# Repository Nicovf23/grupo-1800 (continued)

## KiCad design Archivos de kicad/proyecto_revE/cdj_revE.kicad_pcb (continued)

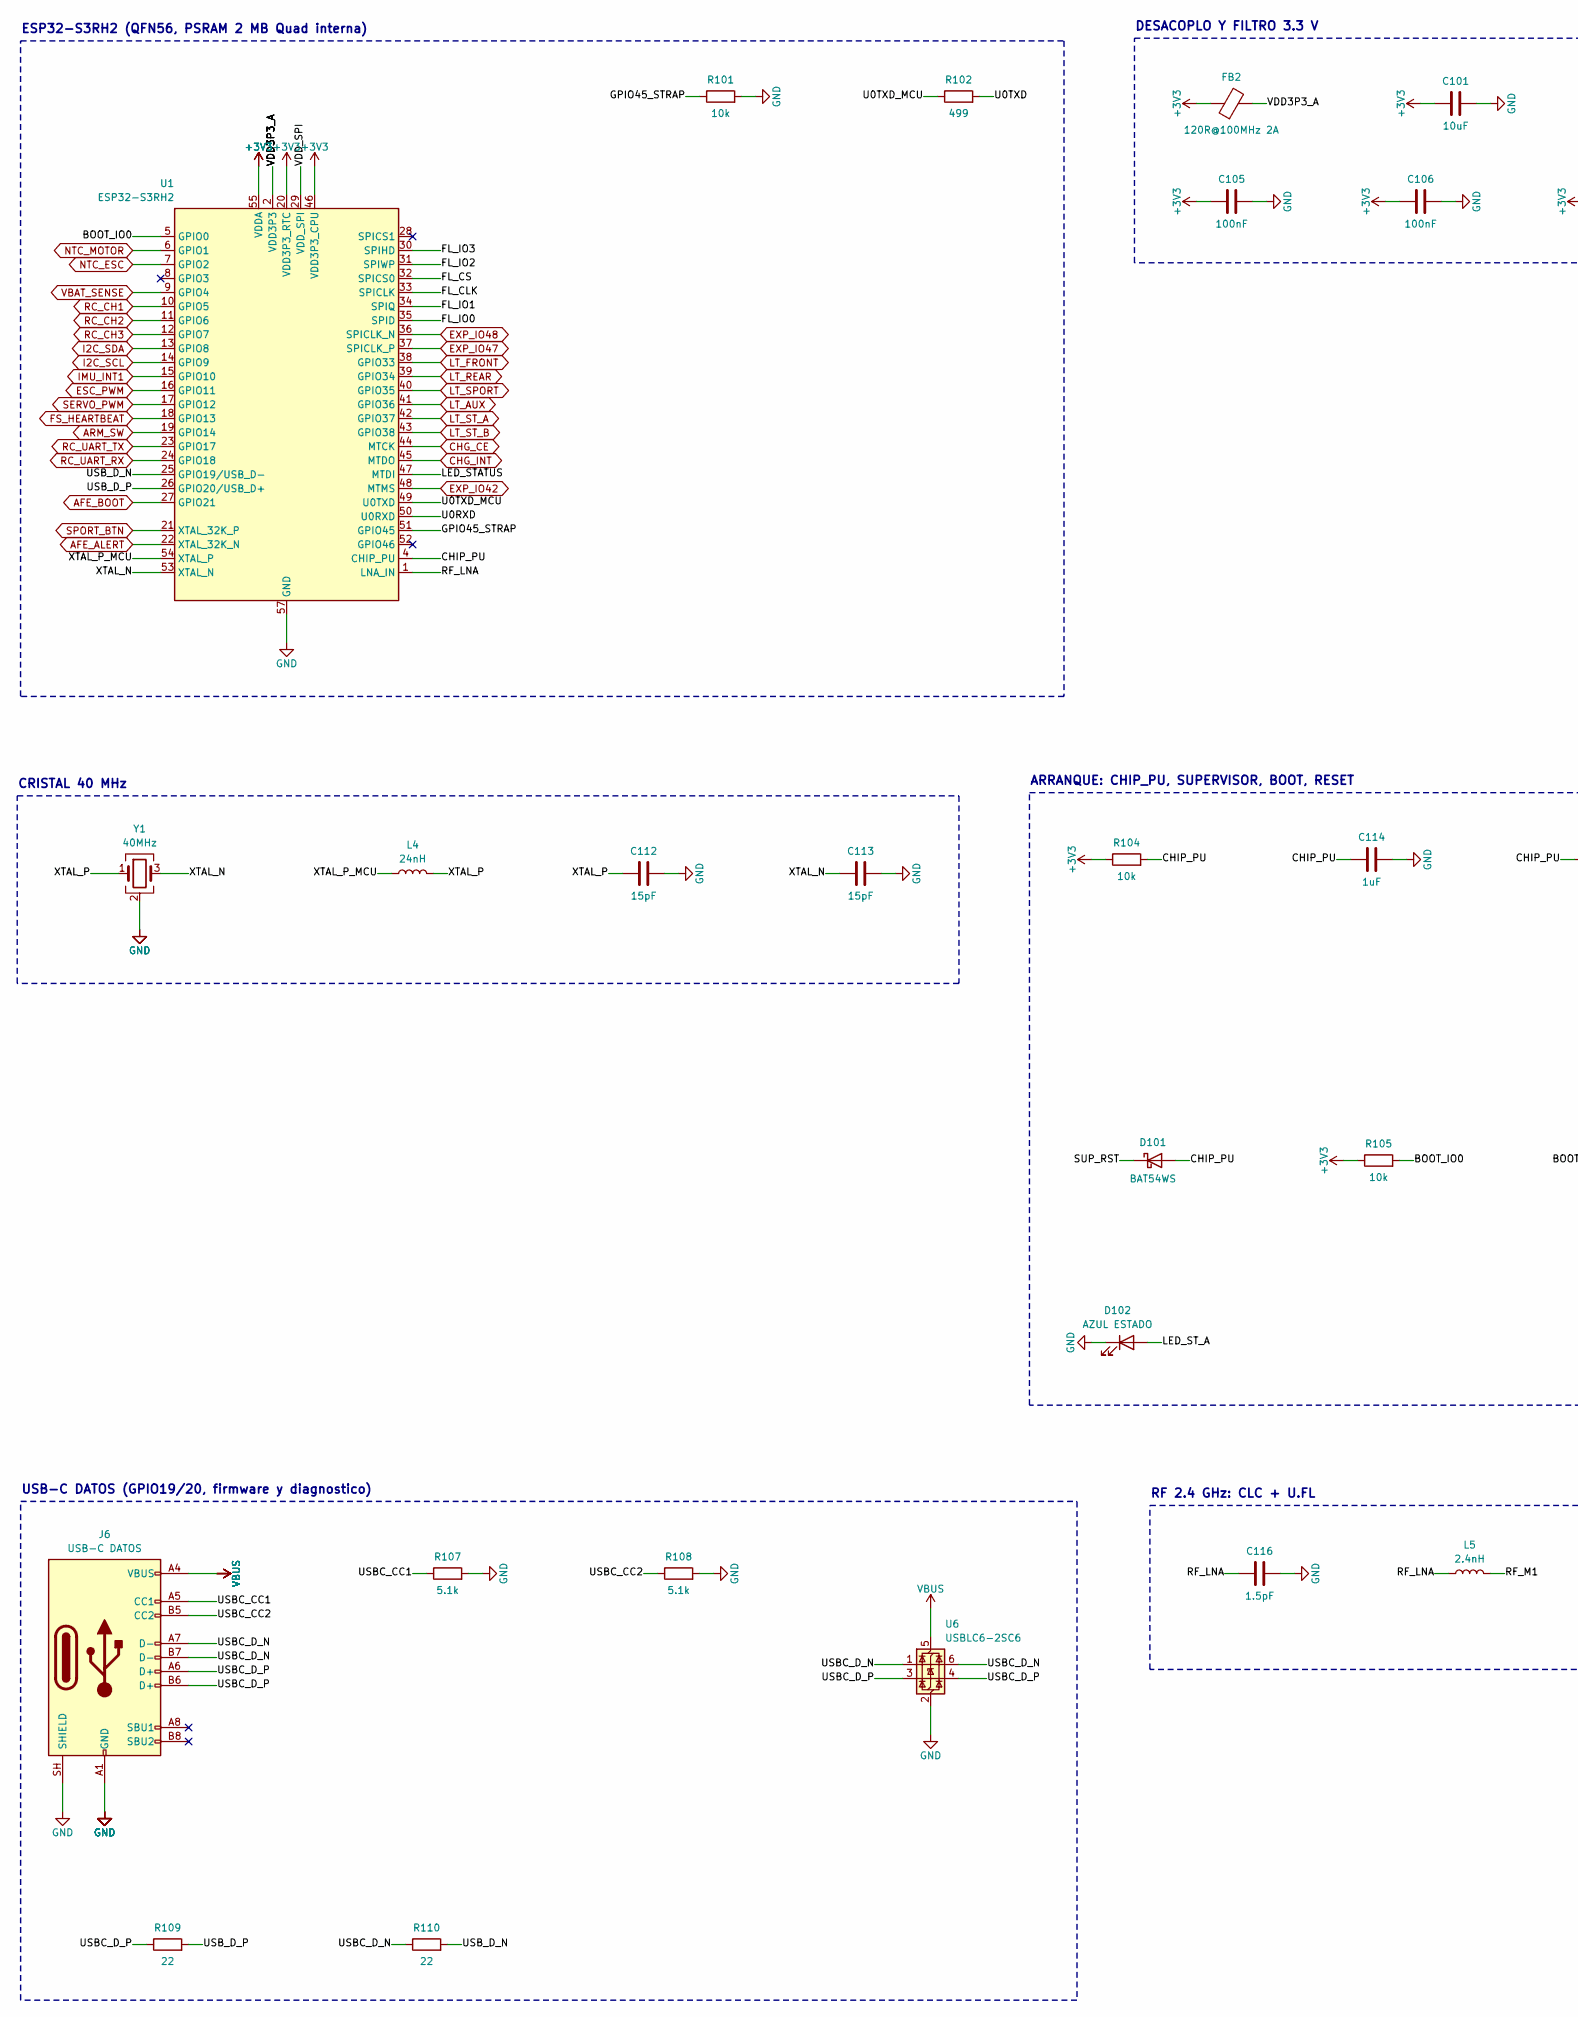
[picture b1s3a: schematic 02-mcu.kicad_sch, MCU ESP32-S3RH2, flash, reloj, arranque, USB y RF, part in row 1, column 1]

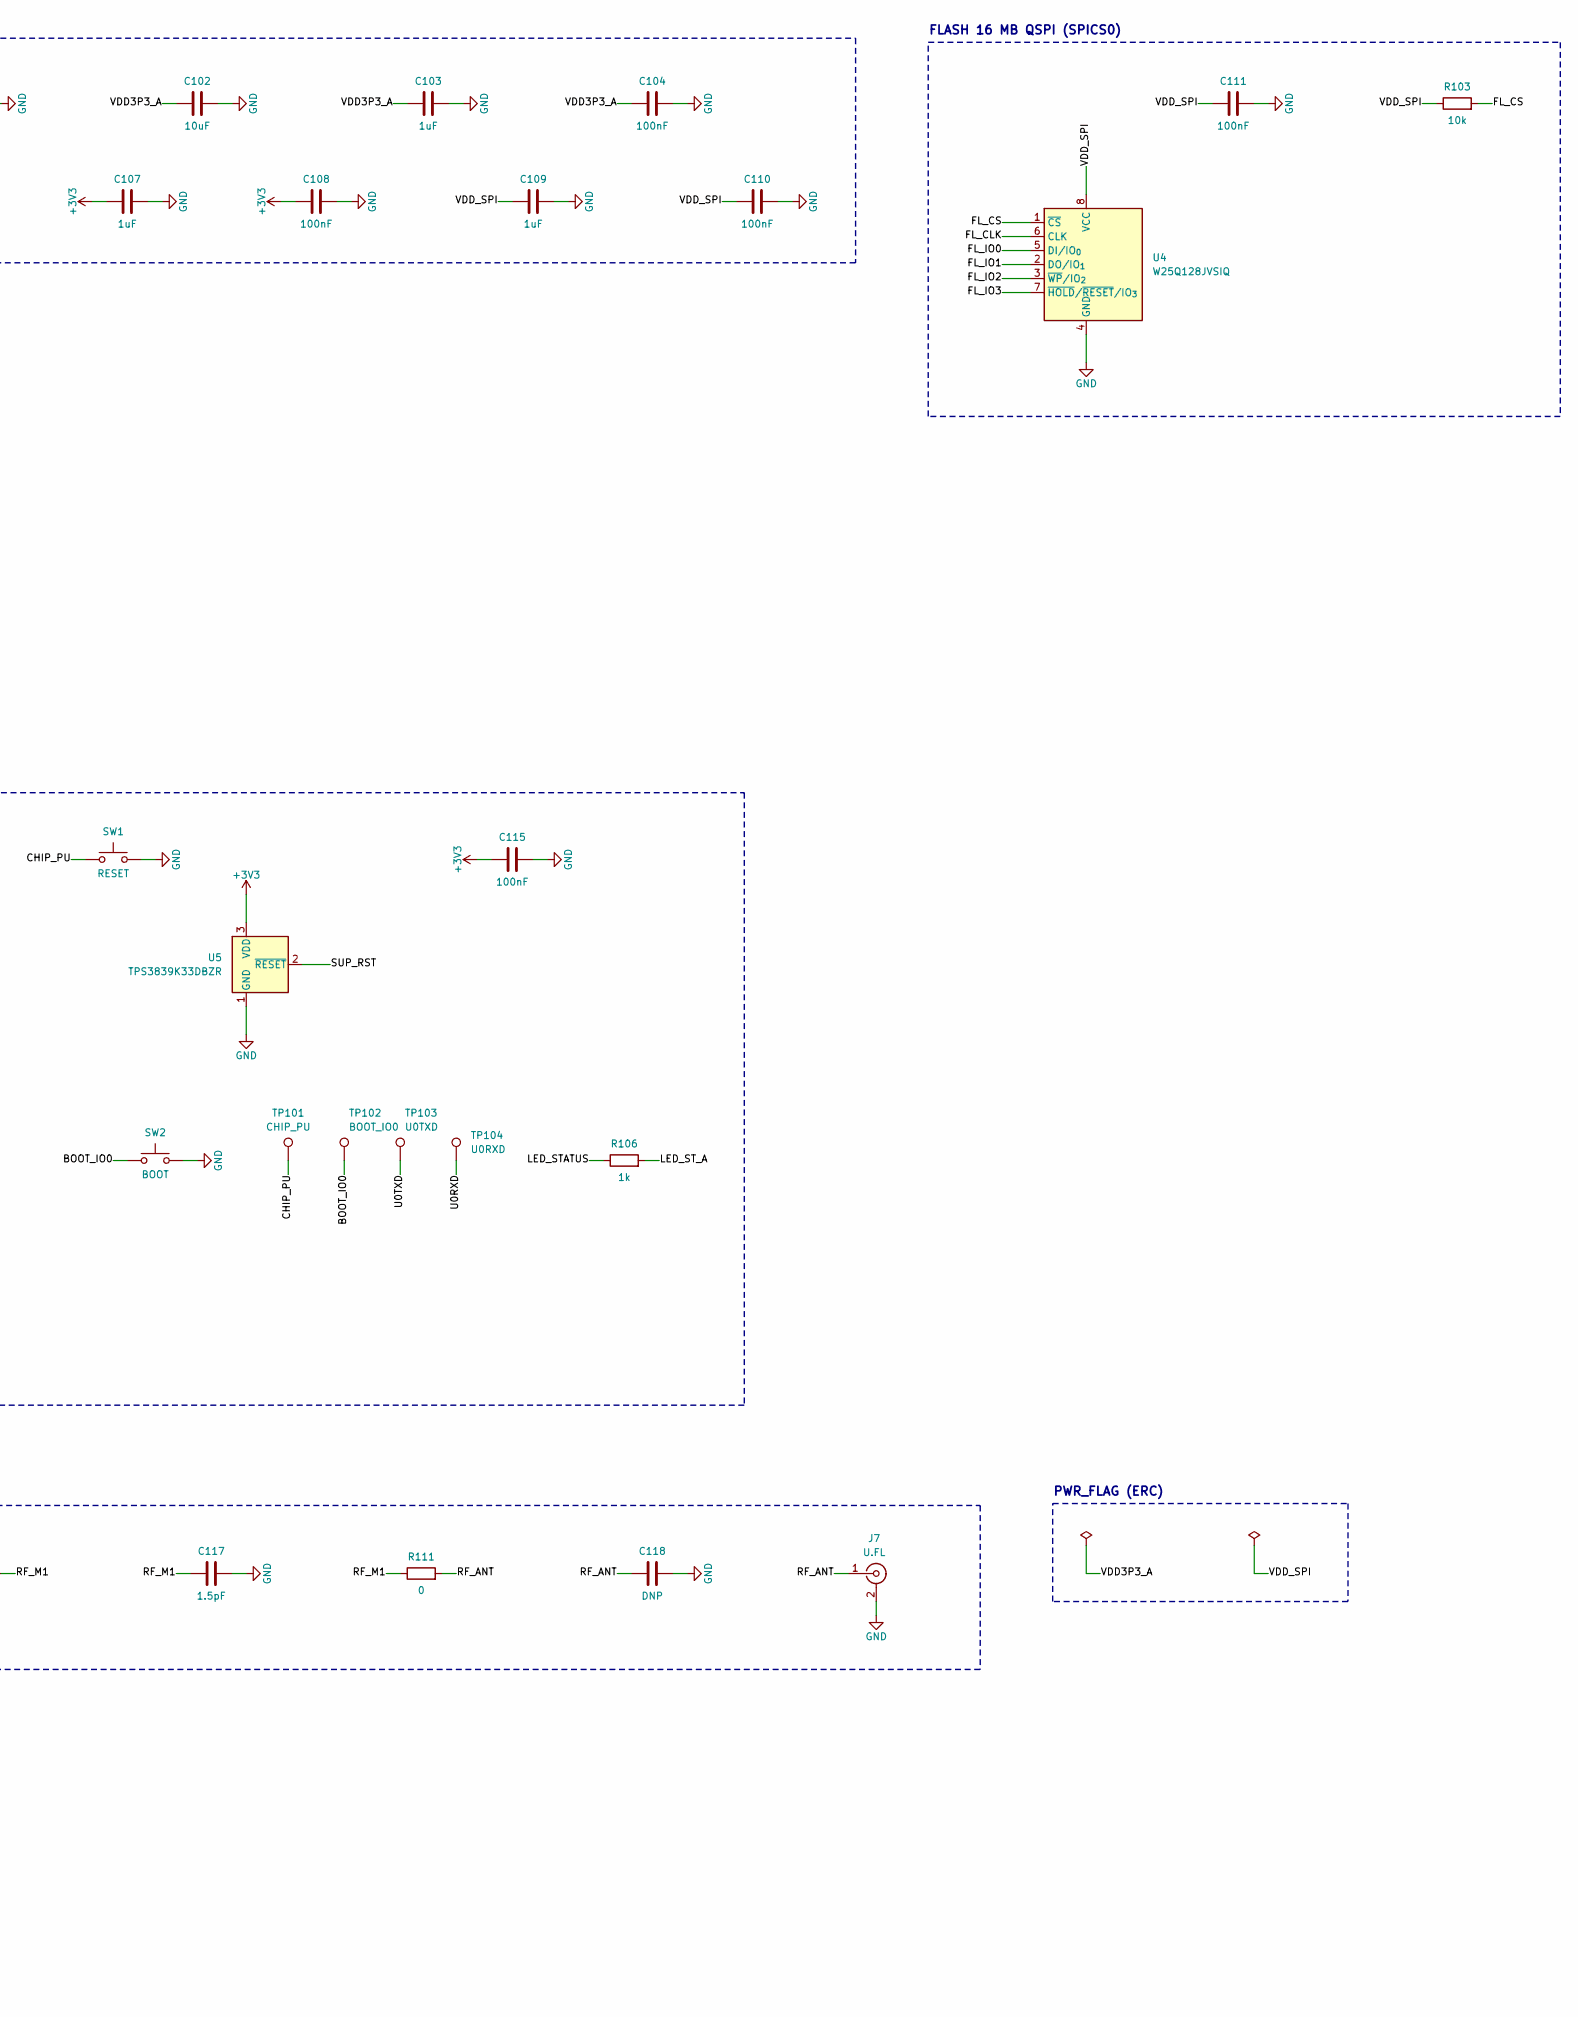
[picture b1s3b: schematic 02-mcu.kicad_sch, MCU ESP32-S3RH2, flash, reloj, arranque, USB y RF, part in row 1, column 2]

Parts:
C101: 10uF; C_0805_2012Metric; MPN X5R 0805 10 V (entrada >= 10 uF, guía)
C102: 10uF; C_0805_2012Metric; MPN X5R 0805 10 V (VDD3P3 pines 2/3)
C103: 1uF; C_0402_1005Metric; MPN X5R 0402
C104: 100nF; C_0402_1005Metric; MPN X7R 0402
C105: 100nF; C_0402_1005Metric; MPN X7R 0402 (VDD3P3_RTC pin 20)
C106: 100nF; C_0402_1005Metric; MPN X7R 0402 (VDD3P3_CPU pin 46)
C107: 1uF; C_0402_1005Metric; MPN X5R 0402 (VDDA pines 55/56)
C108: 100nF; C_0402_1005Metric; MPN X7R 0402 (VDDA pines 55/56)
C109: 1uF; C_0402_1005Metric; MPN X5R 0402 (VDD_SPI, guía: 0.1 + 1 uF)
C110: 100nF; C_0402_1005Metric; MPN X7R 0402 (VDD_SPI)
C111: 100nF; C_0402_1005Metric; MPN X7R 0402 (junto a U4 pin 8)
C112: 15pF; C_0402_1005Metric; MPN C0G 0402 (CL=10 pF: 2x(CL-Cstray); ajus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
C113: 15pF; C_0402_1005Metric; MPN C0G 0402 (ajustar con prueba TX)
C114: 1uF; C_0603_1608Metric; MPN X5R 0603
C115: 100nF; C_0402_1005Metric; MPN X7R 0402 (VDD supervisor)
C116: 1.5pF; C_0201_0603Metric; MPN C0G 0201 (C11 1.2-1.8 pF, guía; ajustar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
C117: 1.5pF; C_0201_0603Metric; MPN C0G 0201 (C12 1.2-1.8 pF, guía)
C118: DNP; C_0201_0603Metric; MPN Sin montar (adaptación lado antena)
D101: BAT54WS; D_SOD-323; MPN BAT54WS (solo tira CHIP_PU hacia abajo)
D102: AZUL ESTADO; LED_0603_1608Metric; MPN LED 0603
FB2: 120R@100MHz 2A; L_0603_1608Metric; MPN A definir en BOM: ferrita 0603 >= 500 mA
J6: USB-C DATOS; USB_C_Receptacle_HRO_TYPE-C-31-M-12; MPN HRO TYPE-C-31-M-12
J7: U.FL; U.FL_Hirose_U.FL-R-SMT-1_Vertical; MPN Hirose U.FL-R-SMT-1(10)
L4: 24nH; L_0402_1005Metric; MPN 0402 24 nH (guía Espressif: serie en XT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
L5: 2.4nH; L_0201_0603Metric; MPN 0201 (L2 2.0-3.0 nH, guía; ajustar con 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
R101: 10k; R_0603_1608Metric; MPN 1 % 0603 (GPIO45=0 -> VDD_SPI 3.3 V)
R102: 499; R_0603_1608Metric; MPN 1 % 0603 (guía Espressif: 499 R en U0TX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
R103: 10k; R_0603_1608Metric; MPN 1 % 0603 (CS en reposo alto)
R104: 10k; R_0603_1608Metric; MPN 1 % 0603 (RC guía: 10k / 1 uF)
R105: 10k; R_0603_1608Metric; MPN 1 % 0603 (pull-up GPIO0)
R106: 1k; R_0603_1608Metric; MPN 1 % 0603
R107, R108: 5.1k; R_0603_1608Metric; MPN 1 % 0603 (sumidero 5 V)
R109, R110: 22; R_0402_1005Metric; MPN 1 % 0402 (guía: 22/33 R)
R111: 0; R_0201_0603Metric; MPN 0 R 0201 (red de antena, ajustable)
SW1: RESET; SW_SPST_TL3342; MPN Pulsador SMD
SW2: BOOT; SW_SPST_TL3342; MPN Pulsador SMD
TP101: CHIP_PU; TestPoint_Pad_D1.5mm; MPN Pad de prueba
TP102: BOOT_IO0; TestPoint_Pad_D1.5mm; MPN Pad de prueba
TP103: U0TXD; TestPoint_Pad_D1.5mm; MPN Pad de prueba
TP104: U0RXD; TestPoint_Pad_D1.5mm; MPN Pad de prueba
U1: ESP32-S3RH2; QFN-56-1EP_7x7mm_P0.4mm_EP4x4mm; MPN Espressif ESP32-S3RH2 (DS v2.2 tabla 1-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
U4: W25Q128JVSIQ; SOIC-8_5.3x5.3mm_P1.27mm; MPN Winbond W25Q128JVSIQ 16 MB 3.3 V (NO va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
U5: TPS3839K33DBZR; SOT-23; MPN TI TPS3839K33DBZR (VIT- 2.93 V, td 200 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
U6: USBLC6-2SC6; SOT-23-6; MPN ST USBLC6-2SC6
Y1: 40MHz; Crystal_SMD_3225-4Pin_3.2x2.5mm; MPN A definir en BOM: 40 MHz +-10 ppm, CL 1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

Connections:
/MCU ESP32-S3RH2, flash, reloj, arranque, USB y RF/BOOT_IO0: R105.2, SW2.1, TP102.1, U1.5 (GPIO0)
/MCU ESP32-S3RH2, flash, reloj, arranque, USB y RF/CHIP_PU: C114.1, D101.2 (A), R104.2, SW1.1, TP101.1, U1.4 (CHIP_PU)
/MCU ESP32-S3RH2, flash, reloj, arranque, USB y RF/FL_CLK: U1.33 (SPICLK), U4.6 (CLK)
/MCU ESP32-S3RH2, flash, reloj, arranque, USB y RF/FL_CS: R103.2, U1.32 (SPICS0), U4.1 (~CS)
/MCU ESP32-S3RH2, flash, reloj, arranque, USB y RF/FL_IO0: U1.35 (SPID), U4.5 (DI/IO_{0})
/MCU ESP32-S3RH2, flash, reloj, arranque, USB y RF/FL_IO1: U1.34 (SPIQ), U4.2 (DO/IO_{1})
/MCU ESP32-S3RH2, flash, reloj, arranque, USB y RF/FL_IO2: U1.31 (SPIWP), U4.3 (~WP/IO_{2})
/MCU ESP32-S3RH2, flash, reloj, arranque, USB y RF/FL_IO3: U1.30 (SPIHD), U4.7 (~HOLD/~RESET/IO_{3})
/MCU ESP32-S3RH2, flash, reloj, arranque, USB y RF/GPIO45_STRAP: R101.1, U1.51 (GPIO45)
/MCU ESP32-S3RH2, flash, reloj, arranque, USB y RF/LED_STATUS: R106.1, U1.47 (MTDI)
/MCU ESP32-S3RH2, flash, reloj, arranque, USB y RF/LED_ST_A: D102.2 (A), R106.2
/MCU ESP32-S3RH2, flash, reloj, arranque, USB y RF/RF_ANT: C118.1, J7.1 (In), R111.2
/MCU ESP32-S3RH2, flash, reloj, arranque, USB y RF/RF_LNA: C116.1, L5.1, U1.1 (LNA_IN)
/MCU ESP32-S3RH2, flash, reloj, arranque, USB y RF/RF_M1: C117.1, L5.2, R111.1
/MCU ESP32-S3RH2, flash, reloj, arranque, USB y RF/SUP_RST: D101.1 (K), U5.2 (~RESET)
/MCU ESP32-S3RH2, flash, reloj, arranque, USB y RF/U0RXD: TP104.1, U1.50 (U0RXD)
/MCU ESP32-S3RH2, flash, reloj, arranque, USB y RF/U0TXD: R102.2, TP103.1
/MCU ESP32-S3RH2, flash, reloj, arranque, USB y RF/U0TXD_MCU: R102.1, U1.49 (U0TXD)
/MCU ESP32-S3RH2, flash, reloj, arranque, USB y RF/USBC_CC1: J6.A5 (CC1), R107.1
/MCU ESP32-S3RH2, flash, reloj, arranque, USB y RF/USBC_CC2: J6.B5 (CC2), R108.1
/MCU ESP32-S3RH2, flash, reloj, arranque, USB y RF/USBC_D_N: J6.A7 (D-), J6.B7 (D-), R110.1, U6.1 (I/O1), U6.6 (I/O1)
/MCU ESP32-S3RH2, flash, reloj, arranque, USB y RF/USBC_D_P: J6.A6 (D+), J6.B6 (D+), R109.1, U6.3 (I/O2), U6.4 (I/O2)
/MCU ESP32-S3RH2, flash, reloj, arranque, USB y RF/USB_D_N: R110.2, U1.25 (GPIO19/USB_D-)
/MCU ESP32-S3RH2, flash, reloj, arranque, USB y RF/USB_D_P: R109.2, U1.26 (GPIO20/USB_D+)
/MCU ESP32-S3RH2, flash, reloj, arranque, USB y RF/XTAL_N: C113.1, U1.53 (XTAL_N), Y1.3
/MCU ESP32-S3RH2, flash, reloj, arranque, USB y RF/XTAL_P: C112.1, L4.2, Y1.1
/MCU ESP32-S3RH2, flash, reloj, arranque, USB y RF/XTAL_P_MCU: L4.1, U1.54 (XTAL_P)
AFE_ALERT: U1.22 (XTAL_32K_N); also elsewhere on the board
AFE_BOOT: U1.27 (GPIO21); also elsewhere on the board
ARM_SW: U1.19 (GPIO14); also elsewhere on the board
CHG_CE: U1.44 (MTCK); also elsewhere on the board
CHG_INT: U1.45 (MTDO); also elsewhere on the board
ESC_PWM: U1.16 (GPIO11); also elsewhere on the board
EXP_IO42: U1.48 (MTMS); also elsewhere on the board
EXP_IO47: U1.37 (SPICLK_P); also elsewhere on the board
EXP_IO48: U1.36 (SPICLK_N); also elsewhere on the board
FS_HEARTBEAT: U1.18 (GPIO13); also elsewhere on the board
I2C_SCL: U1.14 (GPIO9); also elsewhere on the board
I2C_SDA: U1.13 (GPIO8); also elsewhere on the board
IMU_INT1: U1.15 (GPIO10); also elsewhere on the board
LT_AUX: U1.41 (GPIO36); also elsewhere on the board
LT_FRONT: U1.38 (GPIO33); also elsewhere on the board
LT_REAR: U1.39 (GPIO34); also elsewhere on the board
LT_SPORT: U1.40 (GPIO35); also elsewhere on the board
LT_ST_A: U1.42 (GPIO37); also elsewhere on the board
LT_ST_B: U1.43 (GPIO38); also elsewhere on the board
NTC_ESC: U1.7 (GPIO2); also elsewhere on the board
NTC_MOTOR: U1.6 (GPIO1); also elsewhere on the board
RC_CH1: U1.10 (GPIO5); also elsewhere on the board
RC_CH2: U1.11 (GPIO6); also elsewhere on the board
RC_CH3: U1.12 (GPIO7); also elsewhere on the board
RC_UART_RX: U1.24 (GPIO18); also elsewhere on the board
RC_UART_TX: U1.23 (GPIO17); also elsewhere on the board
SERVO_PWM: U1.17 (GPIO12); also elsewhere on the board
SPORT_BTN: U1.21 (XTAL_32K_P); also elsewhere on the board
VBAT_SENSE: U1.9 (GPIO4); also elsewhere on the board

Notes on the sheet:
RF 2.4 GHz: CLC + U.FL
ESP32-S3RH2 (QFN56, PSRAM 2 MB Quad interna)
FLASH 16 MB QSPI (SPICS0)
USB-C DATOS (GPIO19/20, firmware y diagnostico)
CRISTAL 40 MHz
ARRANQUE: CHIP_PU, SUPERVISOR, BOOT, RESET
DESACOPLO Y FILTRO 3.3 V
PWR_FLAG (ERC)

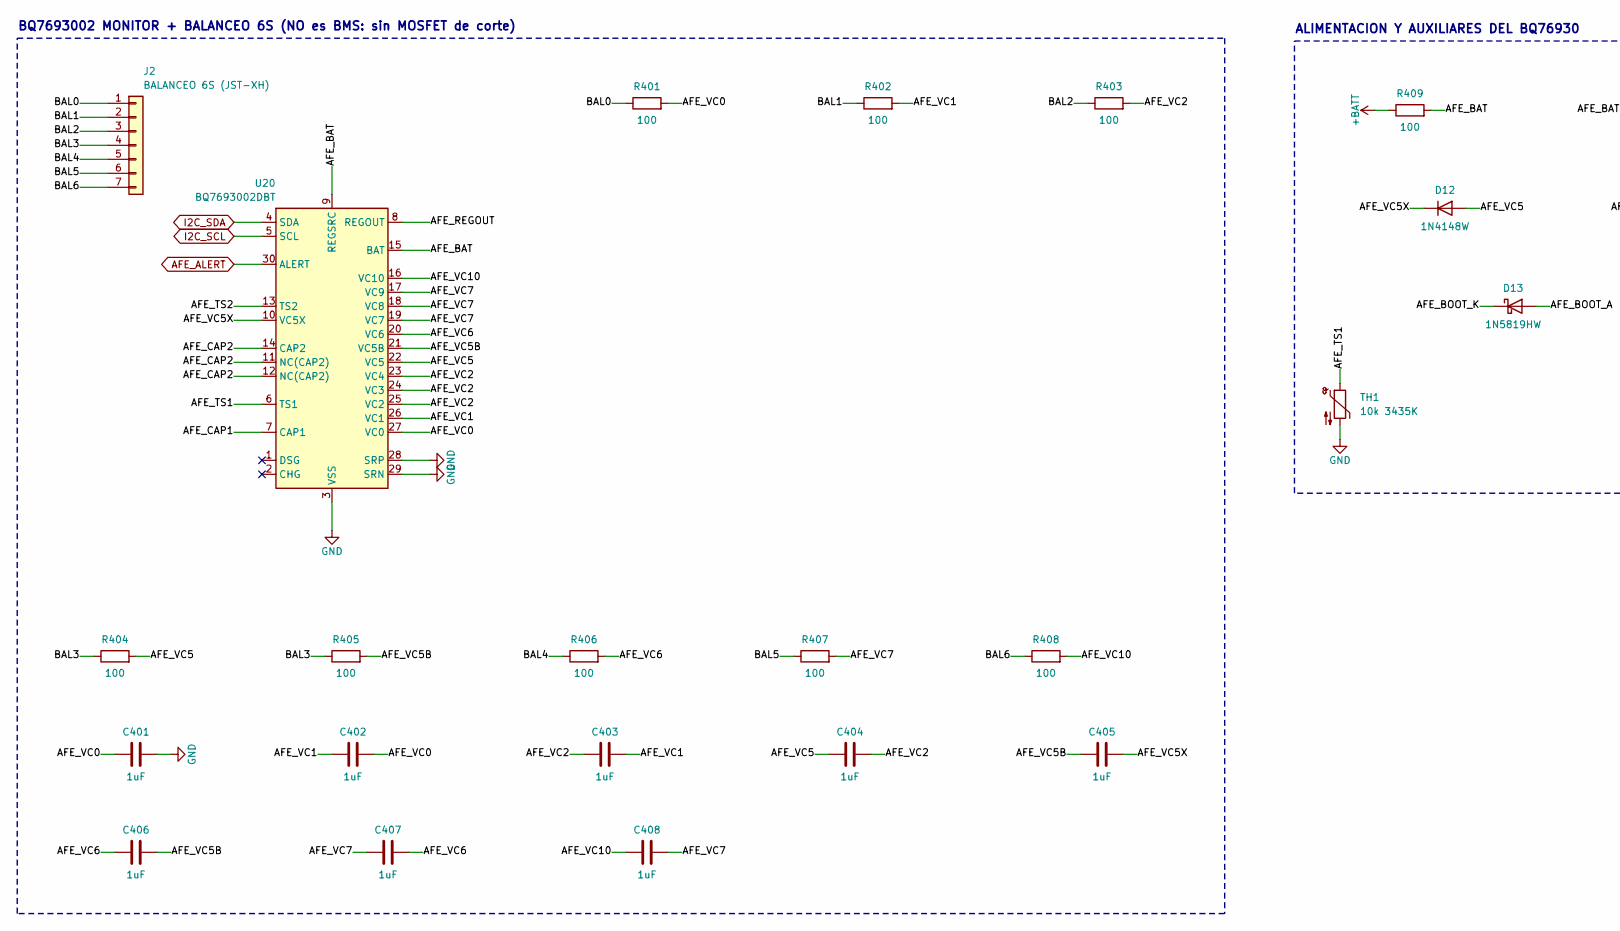
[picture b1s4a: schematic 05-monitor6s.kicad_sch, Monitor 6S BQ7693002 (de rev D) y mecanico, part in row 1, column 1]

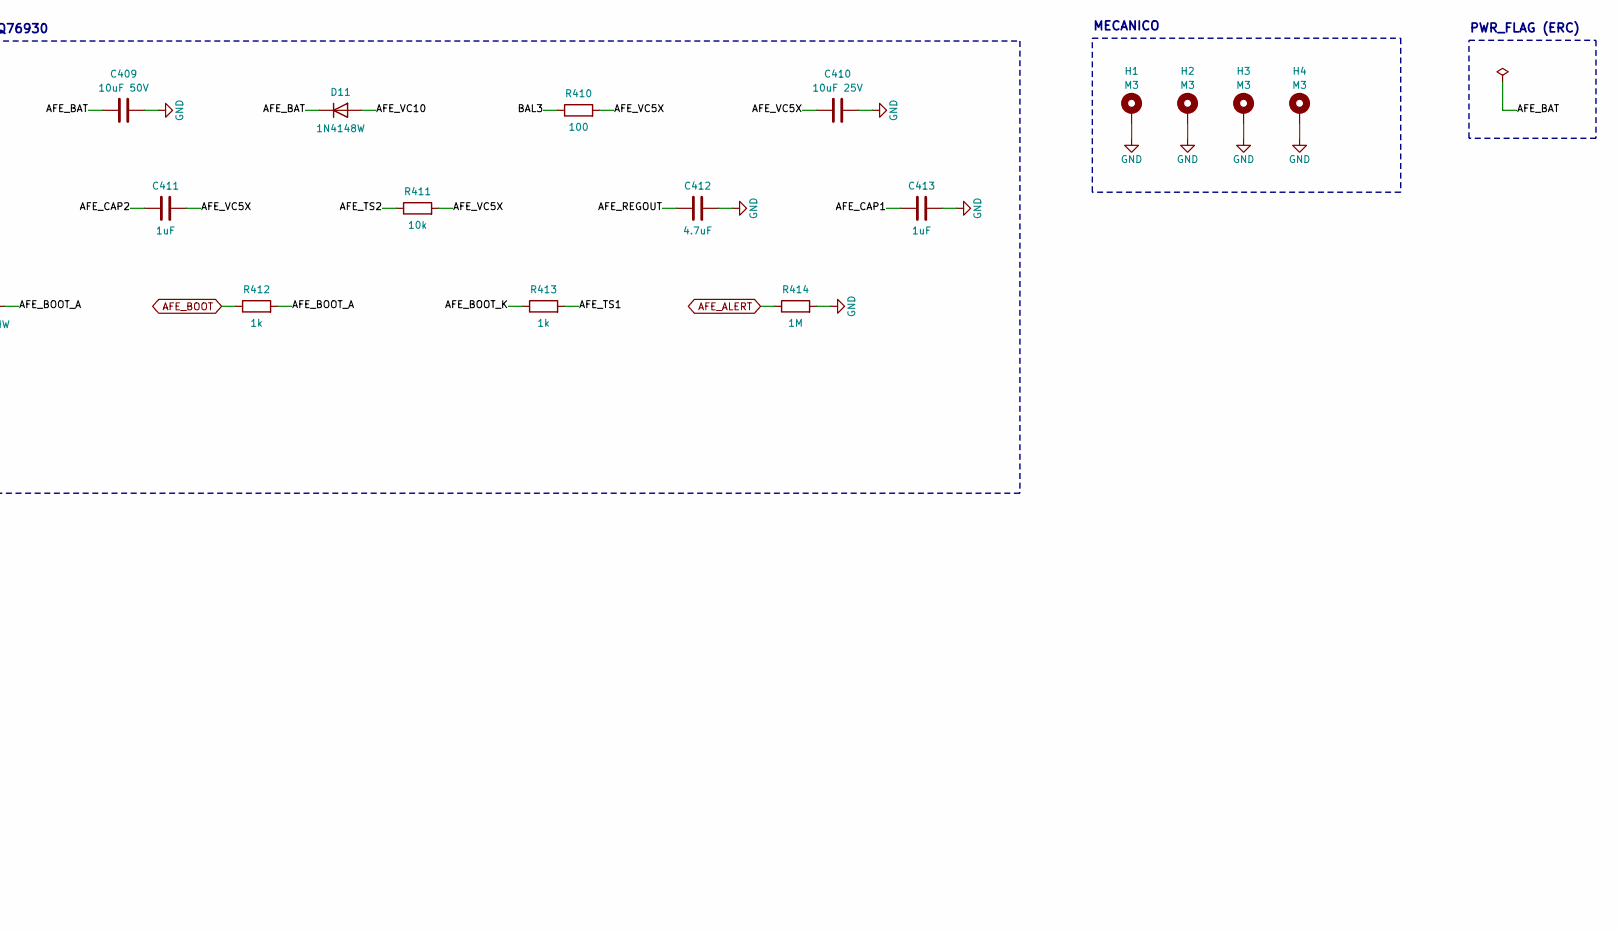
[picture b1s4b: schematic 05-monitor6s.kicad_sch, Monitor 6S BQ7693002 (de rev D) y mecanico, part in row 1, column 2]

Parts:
C401, C402, C403, C404, C405, C406, C407, C408: 1uF; C_0603_1608Metric; MPN X7R 0603 25 V (Cc filtro celda)
C409: 10uF 50V; C_1206_3216Metric; MPN X7R 1206 50 V (Cf BAT)
C410: 10uF 25V; C_0805_2012Metric; MPN X7R 0805 25 V
C411: 1uF; C_0603_1608Metric; MPN X7R 0603 25 V
C412: 4.7uF; C_0805_2012Metric; MPN X7R 0805 10 V
C413: 1uF; C_0603_1608Metric; MPN X7R 0603
D11, D12: 1N4148W; D_SOD-123; MPN Diodes 1N4148W-7-F
D13: 1N5819HW; D_SOD-123; MPN Diodes 1N5819HW-7-F (profesor)
H1, H2, H3, H4: M3; MountingHole_3.2mm_M3_Pad_Via; MPN M3 + arandela antivibración
J2: BALANCEO 6S (JST-XH); JST_XH_B7B-XH-A_1x07_P2.50mm_Vertical; MPN JST B7B-XH-A
R401, R402, R403, R404, R405, R406, R407, R408: 100; R_0603_1608Metric; MPN 1 % 0603 (Rc filtro celda)
R409: 100; R_0603_1608Metric; MPN 1 % 0603 (Rf BAT)
R410: 100; R_0603_1608Metric; MPN 1 % 0603
R411: 10k; R_0603_1608Metric; MPN 1 % 0603
R412, R413: 1k; R_0603_1608Metric; MPN 1 % 0603
R414: 1M; R_0603_1608Metric; MPN 1 % 0603
TH1: 10k 3435K; R_0603_1608Metric; MPN Murata NCP18XH103F03RB
U20: BQ7693002DBT; TSSOP-30_4.4x7.8mm_P0.5mm; MPN TI BQ7693002DBTR (REGOUT 3.3 V, I2C 0x0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

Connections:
/Monitor 6S BQ7693002 (de rev D) y mecanico/AFE_BAT: C409.1, D11.1 (K), R409.2, U20.9 (REGSRC), U20.15 (BAT)
/Monitor 6S BQ7693002 (de rev D) y mecanico/AFE_BOOT_A: D13.2 (A), R412.2
/Monitor 6S BQ7693002 (de rev D) y mecanico/AFE_BOOT_K: D13.1 (K), R413.1
/Monitor 6S BQ7693002 (de rev D) y mecanico/AFE_CAP1: C413.1, U20.7 (CAP1)
/Monitor 6S BQ7693002 (de rev D) y mecanico/AFE_CAP2: C411.1, U20.11 (NC(CAP2)), U20.12 (NC(CAP2)), U20.14 (CAP2)
/Monitor 6S BQ7693002 (de rev D) y mecanico/AFE_REGOUT: C412.1, U20.8 (REGOUT)
/Monitor 6S BQ7693002 (de rev D) y mecanico/AFE_TS1: R413.2, TH1.1, U20.6 (TS1)
/Monitor 6S BQ7693002 (de rev D) y mecanico/AFE_TS2: R411.1, U20.13 (TS2)
/Monitor 6S BQ7693002 (de rev D) y mecanico/AFE_VC0: C401.1, C402.2, R401.2, U20.27 (VC0)
/Monitor 6S BQ7693002 (de rev D) y mecanico/AFE_VC1: C402.1, C403.2, R402.2, U20.26 (VC1)
/Monitor 6S BQ7693002 (de rev D) y mecanico/AFE_VC2: C403.1, C404.2, R403.2, U20.23 (VC4), U20.24 (VC3), U20.25 (VC2)
/Monitor 6S BQ7693002 (de rev D) y mecanico/AFE_VC5: C404.1, D12.2 (A), R404.2, U20.22 (VC5)
/Monitor 6S BQ7693002 (de rev D) y mecanico/AFE_VC5B: C405.1, C406.2, R405.2, U20.21 (VC5B)
/Monitor 6S BQ7693002 (de rev D) y mecanico/AFE_VC5X: C405.2, C410.1, C411.2, D12.1 (K), R410.2, R411.2, U20.10 (VC5X)
/Monitor 6S BQ7693002 (de rev D) y mecanico/AFE_VC6: C406.1, C407.2, R406.2, U20.20 (VC6)
/Monitor 6S BQ7693002 (de rev D) y mecanico/AFE_VC7: C407.1, C408.2, R407.2, U20.17 (VC9), U20.18 (VC8), U20.19 (VC7)
/Monitor 6S BQ7693002 (de rev D) y mecanico/AFE_VC10: C408.1, D11.2 (A), R408.2, U20.16 (VC10)
/Monitor 6S BQ7693002 (de rev D) y mecanico/BAL0: J2.1, R401.1
/Monitor 6S BQ7693002 (de rev D) y mecanico/BAL1: J2.2, R402.1
/Monitor 6S BQ7693002 (de rev D) y mecanico/BAL2: J2.3, R403.1
/Monitor 6S BQ7693002 (de rev D) y mecanico/BAL3: J2.4, R404.1, R405.1, R410.1
/Monitor 6S BQ7693002 (de rev D) y mecanico/BAL4: J2.5, R406.1
/Monitor 6S BQ7693002 (de rev D) y mecanico/BAL5: J2.6, R407.1
/Monitor 6S BQ7693002 (de rev D) y mecanico/BAL6: J2.7, R408.1
AFE_ALERT: R414.1, U20.30 (ALERT); also elsewhere on the board
AFE_BOOT: R412.1; also elsewhere on the board
I2C_SCL: U20.5 (SCL); also elsewhere on the board
I2C_SDA: U20.4 (SDA); also elsewhere on the board

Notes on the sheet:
MECANICO
BQ7693002 MONITOR + BALANCEO 6S (NO es BMS: sin MOSFET de corte)
PWR_FLAG (ERC)
ALIMENTACION Y AUXILIARES DEL BQ76930
